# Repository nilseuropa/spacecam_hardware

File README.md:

# SpaceCam Hardware

This repository contains both Eagle and KiCad project files for the spaceCam IR tracker hardware and 3D printable model files for the enclosure.

### Main components
* ESP-12 module
* Pixart sensor *( e.g. from a Nintendo Wiimote )*
* BNO-055 XPlained Pro *( optional IMU cartridge )*

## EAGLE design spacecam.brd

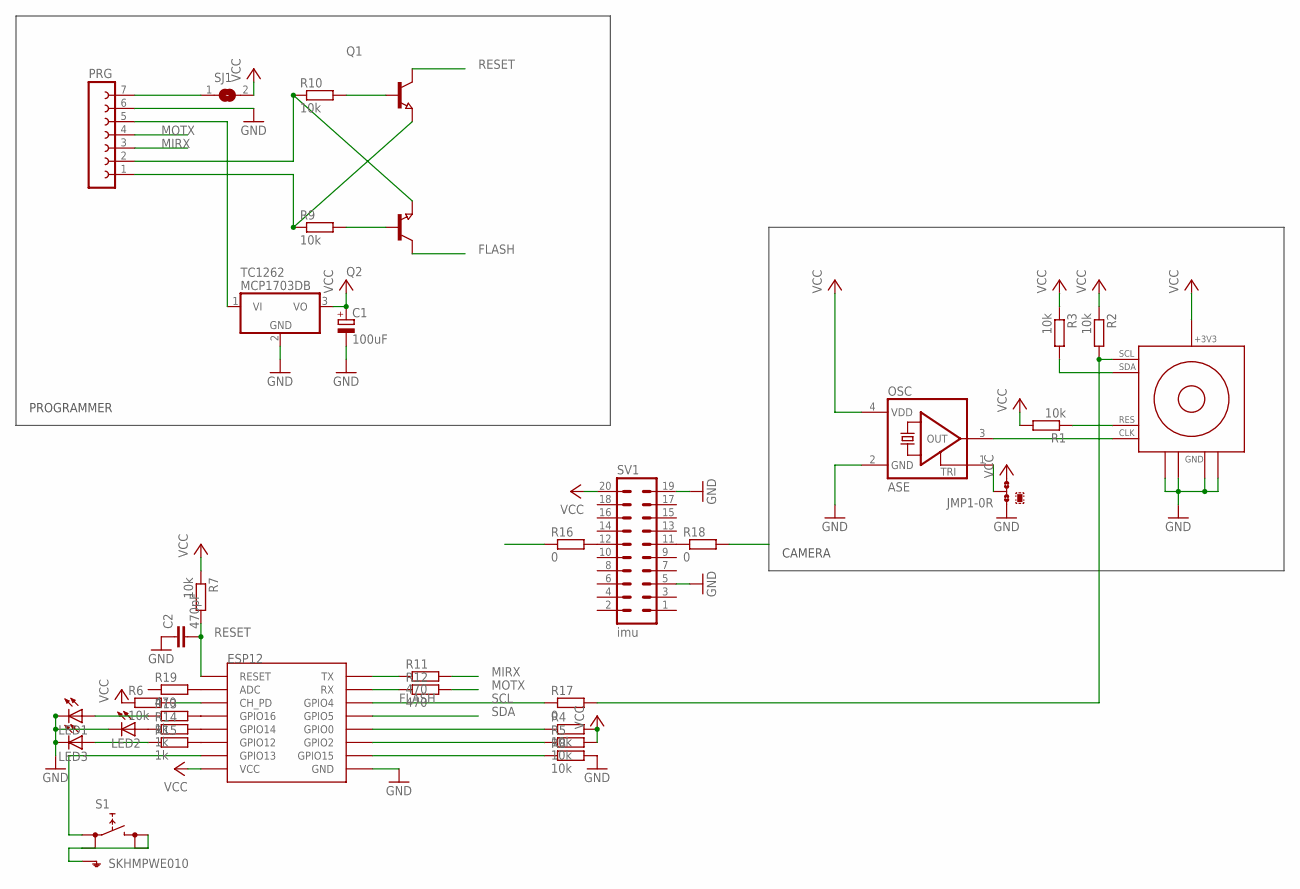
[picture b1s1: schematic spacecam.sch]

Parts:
C1: 100uF; 153CLV-0605
C2: 470pF; C0603
ESP12: ESP12SMD; ESP12-SMD
IR1: Wiimote IR; WII_IR_SENSOR
JMP1: 0R-JUMPB; B0R-JMP
LED1, LED2, LED3: LEDSML0603; SML0603
OSC: ASE
PRG: FE07-1; FE07
Q1, Q2: NPN-TRANSISTOR_SOT23; SOT23
R1, R2, R3, R4, R5, R6, R7, R8, R9, R10: 10k; R0603
R11, R12, R19: 470; R0603
R13, R14, R15: 1k; R0603
R16, R17, R18: 0; R0603
S1: SKHMPWE010; SKHMPXE010
SJ1: SJ
SV1: imu; MA10-2
TC1262: MCP1703DB; SOT223

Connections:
DTR: PRG.2, Q2.2 (E), R10.1
FLASH: ESP12.GPIO0, Q2.3 (C), R4.1
GND: C1.-, C2.1, ESP12.GND, IR1.2_GND@1 (GND), IR1.3_GND@2 (GND), IR1.GND@3 (GND), IR1.GND@4 (GND), JMP1.1, LED1.C, LED2.C, LED3.C, OSC.2 (GND), PRG.6, R8.2, S1.2 (1.2), S1.3 (2.1), S1.4 (2.2), S1.5 (SH), SV1.5, SV1.19, TC1262.2 (GND)
MIRX: PRG.3, R11.2
MOTX: PRG.4, R12.2
unnamed: IR1.7_CLK (CLK), OSC.3 (OUT)
unnamed: JMP1.2, OSC.1 (TRI)
unnamed: IR1.8_RESET (RES), R1.1
unnamed: PRG.7, SJ1.1
unnamed: ESP12.TXD0 (TX), R11.1
unnamed: ESP12.GPIO2, R5.1
unnamed: ESP12.CH_PD, R6.2
unnamed: ESP12.RXD0 (RX), R12.1
unnamed: ESP12.GPIO15, R8.1
unnamed: Q2.1 (B), R9.2
unnamed: Q1.1 (B), R10.2
unnamed: ESP12.GPIO16, R13.2
unnamed: ESP12.GPIO14, R14.2
unnamed: ESP12.GPIO12, R15.2
unnamed: ESP12.GPIO13, S1.1 (1.1)
unnamed: LED1.A, R13.1
unnamed: LED2.A, R14.1
unnamed: LED3.A, R15.1
unnamed: R16.2, SV1.12
unnamed: IR1.5_SCL (SCL), R2.2, R17.2
unnamed: R18.1, SV1.11
unnamed: ESP12.ADC, R19.2
RESET: C2.2, ESP12.RESET, Q1.3 (C), R7.2
RTS: PRG.1, Q1.2 (E), R9.1
SCL: ESP12.GPIO4, R16.1, R17.1
SDA: ESP12.GPIO5, IR1.6_SDA (SDA), R3.2, R18.2
VCC: C1.+, ESP12.VCC, IR1.1_+3V3 (+3V3), JMP1.3, OSC.4 (VDD), R1.2, R2.1, R3.1, R4.2, R5.2, R6.1, R7.1, SJ1.2, SV1.20, TC1262.3 (VO)
VIN: PRG.5, TC1262.1 (VI)

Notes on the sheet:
PROGRAMMER
CAMERA

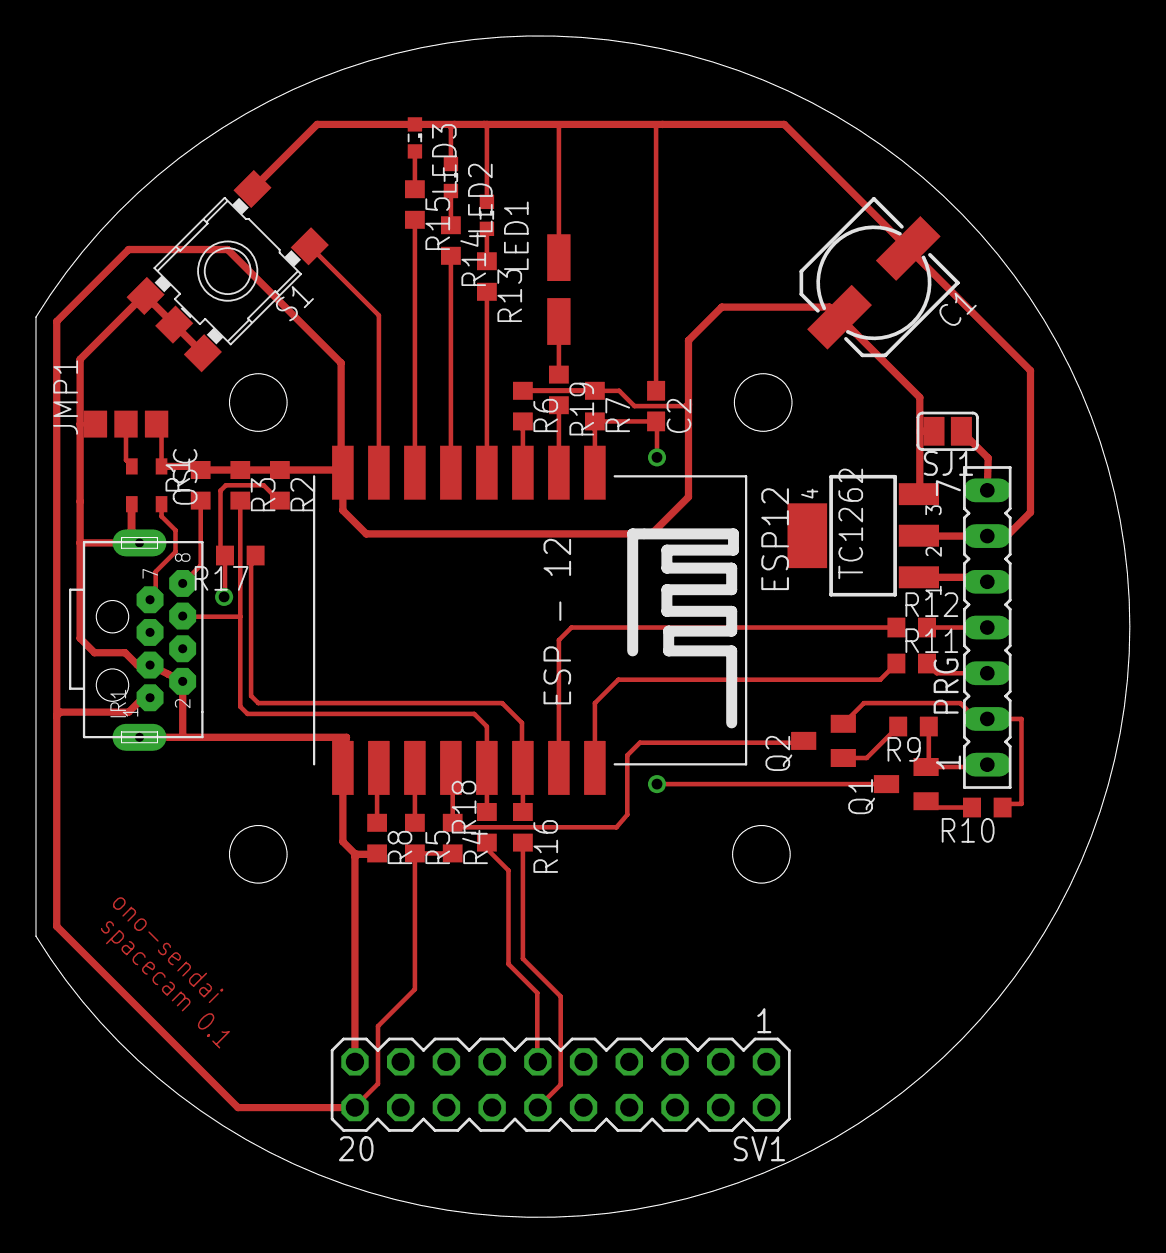
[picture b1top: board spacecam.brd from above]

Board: 2 copper layers, 60.8 x 65.6 mm, 35 parts (0 on the bottom side), 33 nets.

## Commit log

2019-12-16 Create LICENSE
2019-12-16 added design files
